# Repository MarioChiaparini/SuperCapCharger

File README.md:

# SuperCapCharger
Lets charge our Super-Capacitors

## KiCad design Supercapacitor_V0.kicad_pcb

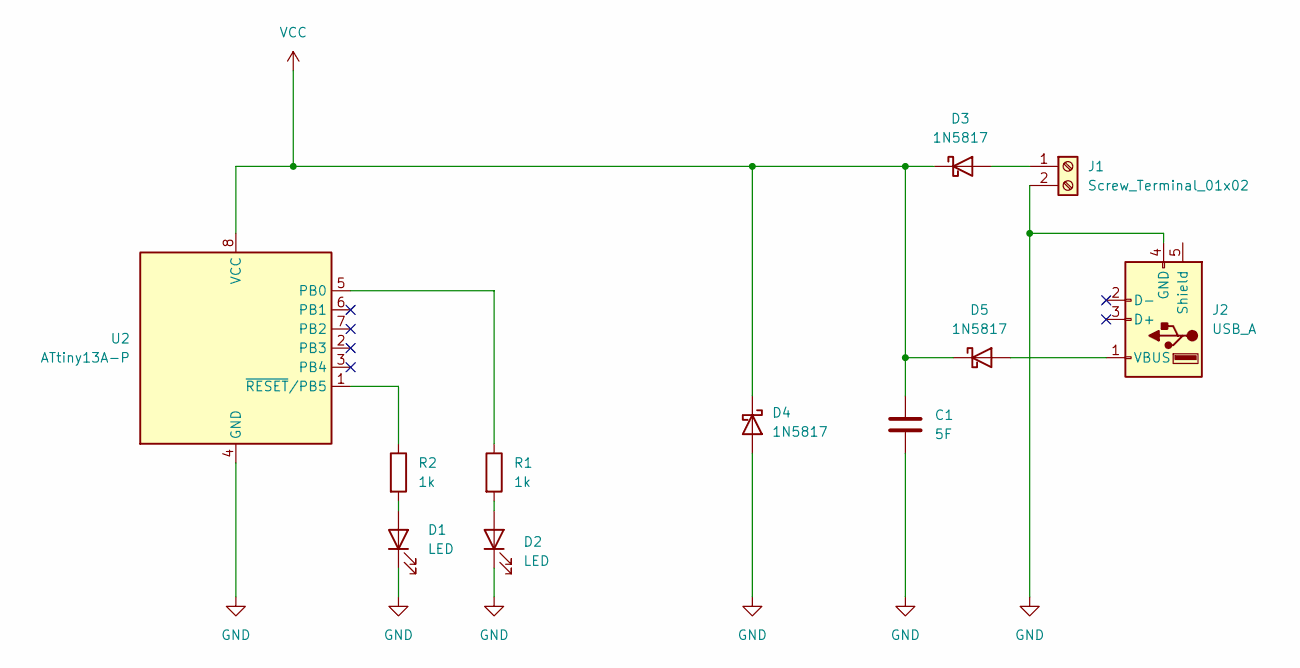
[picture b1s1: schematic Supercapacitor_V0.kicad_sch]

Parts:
C1: 5F; C_Radial_D8.0mm_H11.5mm_P3.50mm
D1, D2: LED; LED_D3.0mm_IRBlack
D3, D4, D5: 1N5817; D_DO-41_SOD81_P10.16mm_Horizontal
J1: Screw_Terminal_01x02; PhoenixContact_MSTBA_2,5_2-G_1x02_P5.00mm_Horizontal
J2: USB_A; USB_A_Molex_105057_Vertical
R1, R2: 1k; R_Axial_DIN0204_L3.6mm_D1.6mm_P5.08mm_Horizontal
U2: ATtiny13A-P; DIP-8_W7.62mm

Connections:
GND: C1.2, D1.1 (K), D2.1 (K), D4.2 (A), J1.2, J2.4 (GND), U2.4 (GND)
unnamed: D1.2 (A), R2.2
unnamed: D2.2 (A), R1.2
unnamed: D3.2 (A), J1.1
unnamed: D5.2 (A), J2.1 (VBUS)
unnamed: R1.1, U2.5 (PB0)
unnamed: R2.1, U2.1 (~RESET/PB5)
VCC: C1.1, D3.1 (K), D4.1 (K), D5.1 (K), U2.8 (VCC)

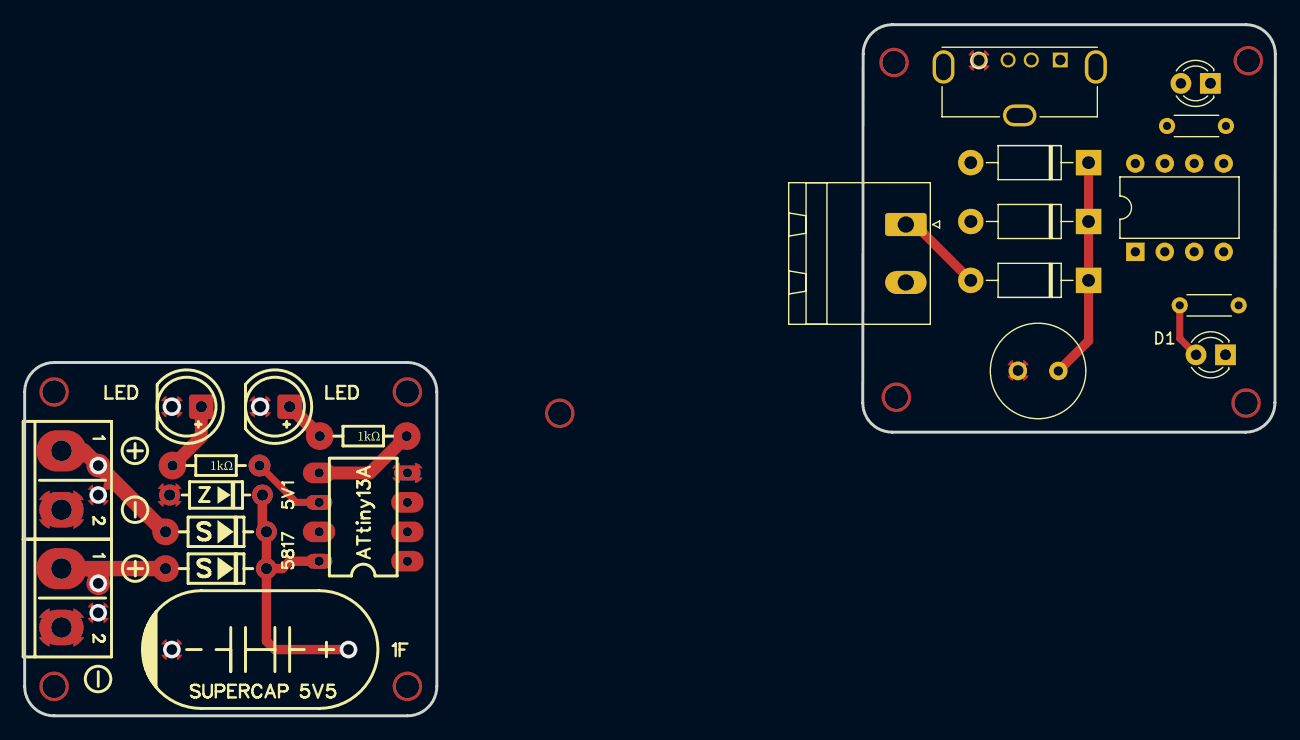
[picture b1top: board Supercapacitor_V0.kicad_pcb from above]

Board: 2 copper layers, 35.6 x 35.2 mm, 11 parts (0 on the bottom side), 8 nets.
